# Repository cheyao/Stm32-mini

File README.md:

# STM32U073 Mini

A small STM32U073 devboard made for low power stuff. It runs off USB-C or a LiPo, and has a LiPo charging circuit. The whole power chain is picked so the board idles at basically nothing when the MCU is asleep.

The STM32U0 is stm's ulp stm32. With a 56MHz Cortex-M0+, 64KB flash, and 40KB SRAM, crystal-less USB, and ~100nA sleep. The board uses a STM32U073K8Ux chip, with 3.3V from a ldo with 25nA Iq.

There's a 32.768kHz crystal for the RTC, so you can sleep for hours and still wake up on time.

This is made for very low-power projects, such as eink control with lots of sleep.

### Features

- [STM32U073K8](https://www.st.com/en/microcontrollers-microprocessors/stm32u073k8.html)
    - Arm Cortex-M0+ @ 56MHz
    - 64KB Flash, 40KB SRAM
    - USB full speed, crystal-less
    - 12bit ADC, comparators, op-amp, LCD controller
- 32.768kHz LSE crystal
- USB-C, programmable over the built-in USB DFU bootloader
- BOOT0 button
- LiPo charging with power path
- SWD header
- 2x15 pin headers
- 18.5x50.3mm

### Pinout

| Pin | Left (J4) | Right (J5) |
| --- | --------- | ---------- |
| 1   | PA10      | VBUS       |
| 2   | PA9       | 5V         |
| 3   | PA8       | GND        |
| 4   | GND       | BATT       |
| 5   | PA15      | GND        |
| 6   | PB3       | 3V3        |
| 7   | PB4       | GND        |
| 8   | PB5       | PB1        |
| 9   | PB6       | PB0        |
| 10  | PB7       | GND        |
| 11  | GND       | PA7        |
| 12  | PA0       | PA6        |
| 13  | PA1       | PA5        |
| 14  | RST       | PA4        |
| 15  | PA2       | PA3        |

SWD header: SWCLK, GND, SWDIO

### Programming

Hold BOOT0, plug it in (or tap RST), and it shows up as a DFU device. Then flash with `dfu-util` or STM32CubeProgrammer:

```
$ dfu-util -a 0 -s 0x08000000:leave -D firmware.bin
```

Or use any SWD probe on the 3 pin header.

### Hardware

KiCad files are in `hardware/`, production files are in `hardware/production/`.

### BOM

| Item | Price | Link |
| --- | --- | --- |
| PCB | $6.15 | jlcpcb.com |
| PCBA | $103.46 | Same |
| Shipping | $23.52 | Same |
| Total | $133.13 | - |

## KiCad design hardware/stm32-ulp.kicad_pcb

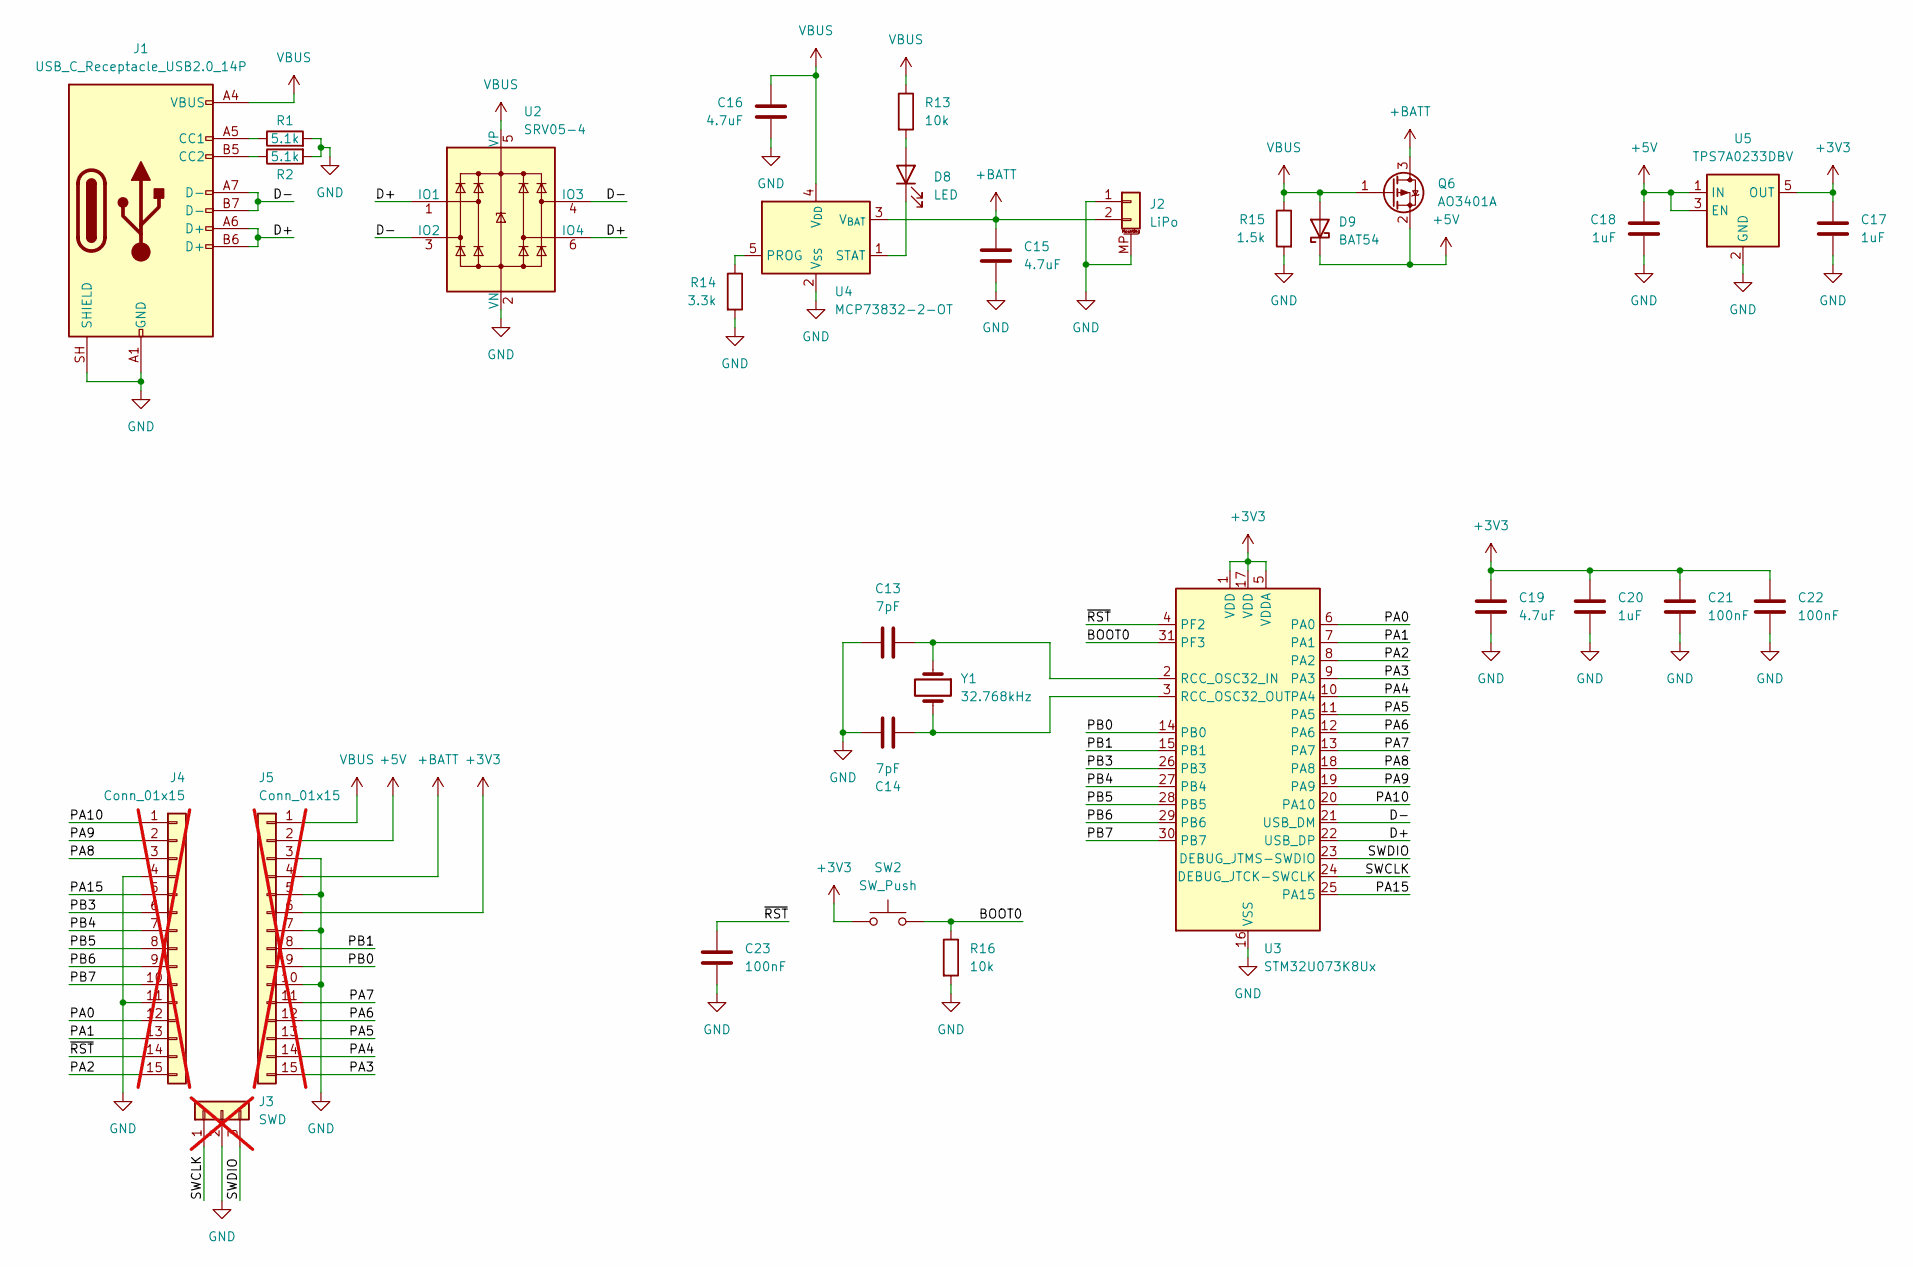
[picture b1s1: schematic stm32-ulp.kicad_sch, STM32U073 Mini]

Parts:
C13, C14: 7pF; C_0402_1005Metric; LCSC Part # C1577
C15, C16, C19: 4.7uF; C_0402_1005Metric; LCSC Part # C23733
C17, C18, C20: 1uF; C_0402_1005Metric; LCSC Part # C52923
C21, C22, C23: 100nF; C_0402_1005Metric; LCSC Part # C307331
D8: LED; LED_0402_1005Metric; LCSC Part # C51933306
D9: BAT54; D_SOD-523; LCSC Part # C81572
J1: USB_C_Receptacle_USB2.0_14P; USB_C_Receptacle_HRO_TYPE-C-31-M-12; LCSC Part # C393939
J2: LiPo; HCTL_JST_PH_HC-PH-2AWT-B_2P; LCSC Part # C19633668
J3: SWD; PinHeader_1x03_P2.54mm_Vertical; not fitted
J4, J5: Conn_01x15; PinHeader_1x15_P2.54mm_Vertical; not fitted
Q6: AO3401A; SOT-23; LCSC Part # C15127
R1, R2: 5.1k; R_0402_1005Metric; LCSC Part # C25905
R13, R16: 10k; R_0402_1005Metric; LCSC Part # C25744
R14: 3.3k; R_0402_1005Metric; LCSC Part # C25890
R15: 1.5k; R_0402_1005Metric; LCSC Part # C25867
SW2: SW_Push; SW_Push_SPST_TSA016; LCSC Part # C2888430
U2: SRV05-4; SOT-23-6; LCSC Part # C85364
U3: STM32U073K8Ux; QFN-32-1EP_5x5mm_P0.5mm_EP3.45x3.45mm_ThermalVias; LCSC Part # C23679798
U4: MCP73832-2-OT; SOT-23-5; LCSC Part # C38066
U5: TPS7A0233DBV; SOT-23-5; LCSC Part # C5142805
Y1: 32.768kHz; Crystal_SMD_3215-2Pin_3.2x1.5mm; LCSC Part # C6491652

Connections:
+3V3: C17.1, C19.1, C20.1, C21.1, C22.1, J5.6, SW2.1, U3.1 (VDD), U3.5 (VDDA), U3.17 (VDD), U5.5 (OUT)
+5V: C18.1, D9.1 (K), J5.2, Q6.2 (S), U5.1 (IN), U5.3 (EN)
+BATT: C15.1, J2.2, J5.4, Q6.3 (D), U4.3 (V_{BAT})
/BOOT0: R16.1, SW2.2, U3.31 (PF3)
/D+: J1.A6 (D+), J1.B6 (D+), U2.1 (IO1), U2.6 (IO4), U3.22 (USB_DP)
/D-: J1.A7 (D-), J1.B7 (D-), U2.3 (IO2), U2.4 (IO3), U3.21 (USB_DM)
/PA0: J4.12, U3.6 (PA0)
/PA1: J4.13, U3.7 (PA1)
/PA2: J4.15, U3.8 (PA2)
/PA3: J5.15, U3.9 (PA3)
/PA4: J5.14, U3.10 (PA4)
/PA5: J5.13, U3.11 (PA5)
/PA6: J5.12, U3.12 (PA6)
/PA7: J5.11, U3.13 (PA7)
/PA8: J4.3, U3.18 (PA8)
/PA9: J4.2, U3.19 (PA9)
/PA10: J4.1, U3.20 (PA10)
/PA15: J4.5, U3.25 (PA15)
/PB0: J5.9, U3.14 (PB0)
/PB1: J5.8, U3.15 (PB1)
/PB3: J4.6, U3.26 (PB3)
/PB4: J4.7, U3.27 (PB4)
/PB5: J4.8, U3.28 (PB5)
/PB6: J4.9, U3.29 (PB6)
/PB7: J4.10, U3.30 (PB7)
/SWCLK: J3.1, U3.24 (DEBUG_JTCK-SWCLK)
/SWDIO: J3.3, U3.23 (DEBUG_JTMS-SWDIO)
/~RST: C23.1, J4.14, U3.4 (PF2)
GND: C13.1, C14.2, C15.2, C16.2, C17.2, C18.2, C19.2, C20.2, C21.2, C22.2, C23.2, J1.A1 (GND), J1.A12 (GND), J1.B1 (GND), J1.B12 (GND), J1.SH (SHIELD), J2.1, J2.MP (MountPin), J3.2, J4.4, J4.11, J5.3, J5.5, J5.7, J5.10, R1.2, R2.2, R14.2, R15.2, R16.2, U2.2 (VN), U3.16 (VSS), U3.32 (VSS), U3.33 (VSS), U4.2 (V_{SS}), U5.2 (GND)
unnamed: D8.2 (A), R13.2
unnamed: D8.1 (K), U4.1 (STAT)
unnamed: J1.A5 (CC1), R1.1
unnamed: J1.B5 (CC2), R2.1
unnamed: C13.2, U3.2 (RCC_OSC32_IN), Y1.1
unnamed: C14.1, U3.3 (RCC_OSC32_OUT), Y1.2
unnamed: R14.1, U4.5 (PROG)
VBUS: C16.1, D9.2 (A), J1.A4 (VBUS), J1.A9 (VBUS), J1.B4 (VBUS), J1.B9 (VBUS), J5.1, Q6.1 (G), R13.1, R15.1, U2.5 (VP), U4.4 (V_{DD})

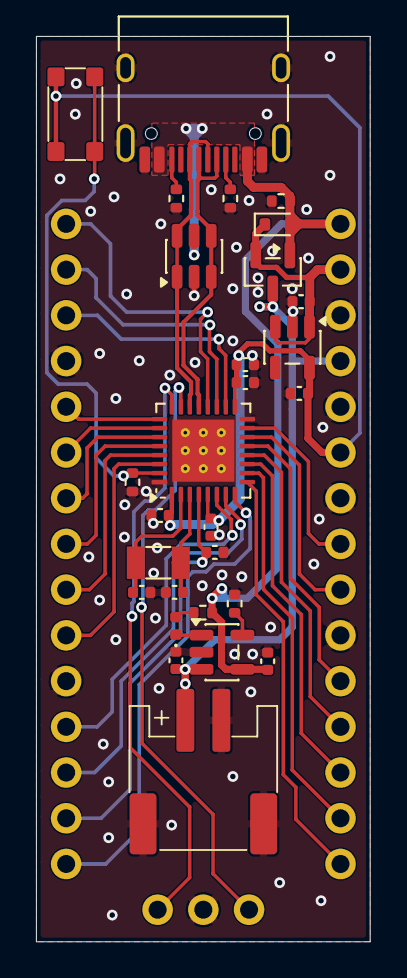
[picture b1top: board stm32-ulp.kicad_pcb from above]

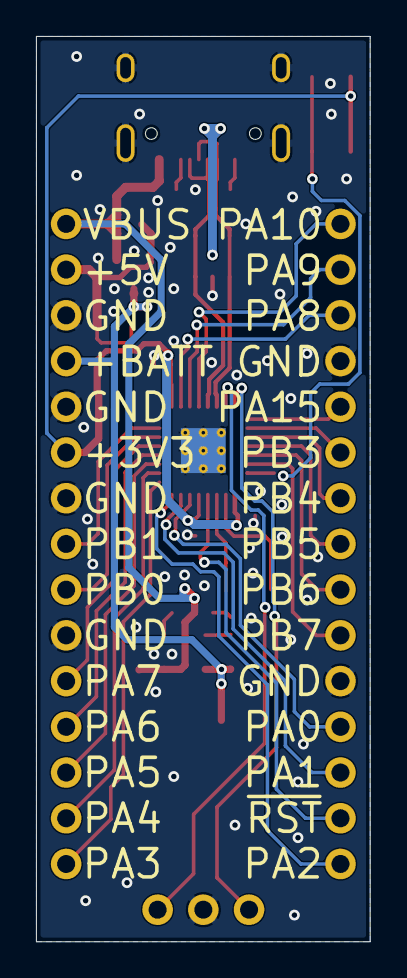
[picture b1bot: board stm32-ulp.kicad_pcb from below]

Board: 2 copper layers, 18.5 x 50.3 mm, 31 parts (3 on the bottom side), 37 nets.

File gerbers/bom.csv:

Designator,Footprint,Quantity,Value,LCSC Part #
"C13, C14",0402,2,7pF,C1577
"C15, C16, C19",0402,3,4.7uF,C23733
"C17, C18, C20",0402,3,1uF,C52923
"C21, C22, C23",0402,3,100nF,C307331
D8,0402,1,LED,C51933306
D9,D_SOD-523,1,BAT54,C81572
J1,USB_C_Receptacle_HRO_TYPE-C-31-M-12,1,USB_C_Receptacle_USB2.0_14P,C393939
J2,HCTL_JST_PH_HC-PH-2AWT-B_2P,1,LiPo,C19633668
J3,PinHeader_1x03_P2.54mm_Vertical,1,SWD,
"J4, J5",PinHeader_1x15_P2.54mm_Vertical,2,Conn_01x15,
Q6,SOT-23,1,AO3401A,C347476
"R1, R2",0402,2,5.1k,C25905
"R13, R16",0402,2,10k,C25744
R14,0402,1,3.3k,C25890
R15,0402,1,1.5k,C25867
SW2,SW_Push_SPST_TSA016,1,SW_Push,C2888430
U2,SOT-23-6,1,SRV05-4,C2836319
U3,QFN-32-1EP_5x5mm_P0.5mm_EP3.45x3.45mm_ThermalVias,1,STM32U073K8Ux,C23679798
U4,SOT-23-5,1,MCP73832-2-OT,C38066
U5,SOT-23-5,1,TPS7A0233DBV,C5142805
Y1,Crystal_SMD_3215-2Pin_3.2x1.5mm,1,32.768kHz,C6491652
